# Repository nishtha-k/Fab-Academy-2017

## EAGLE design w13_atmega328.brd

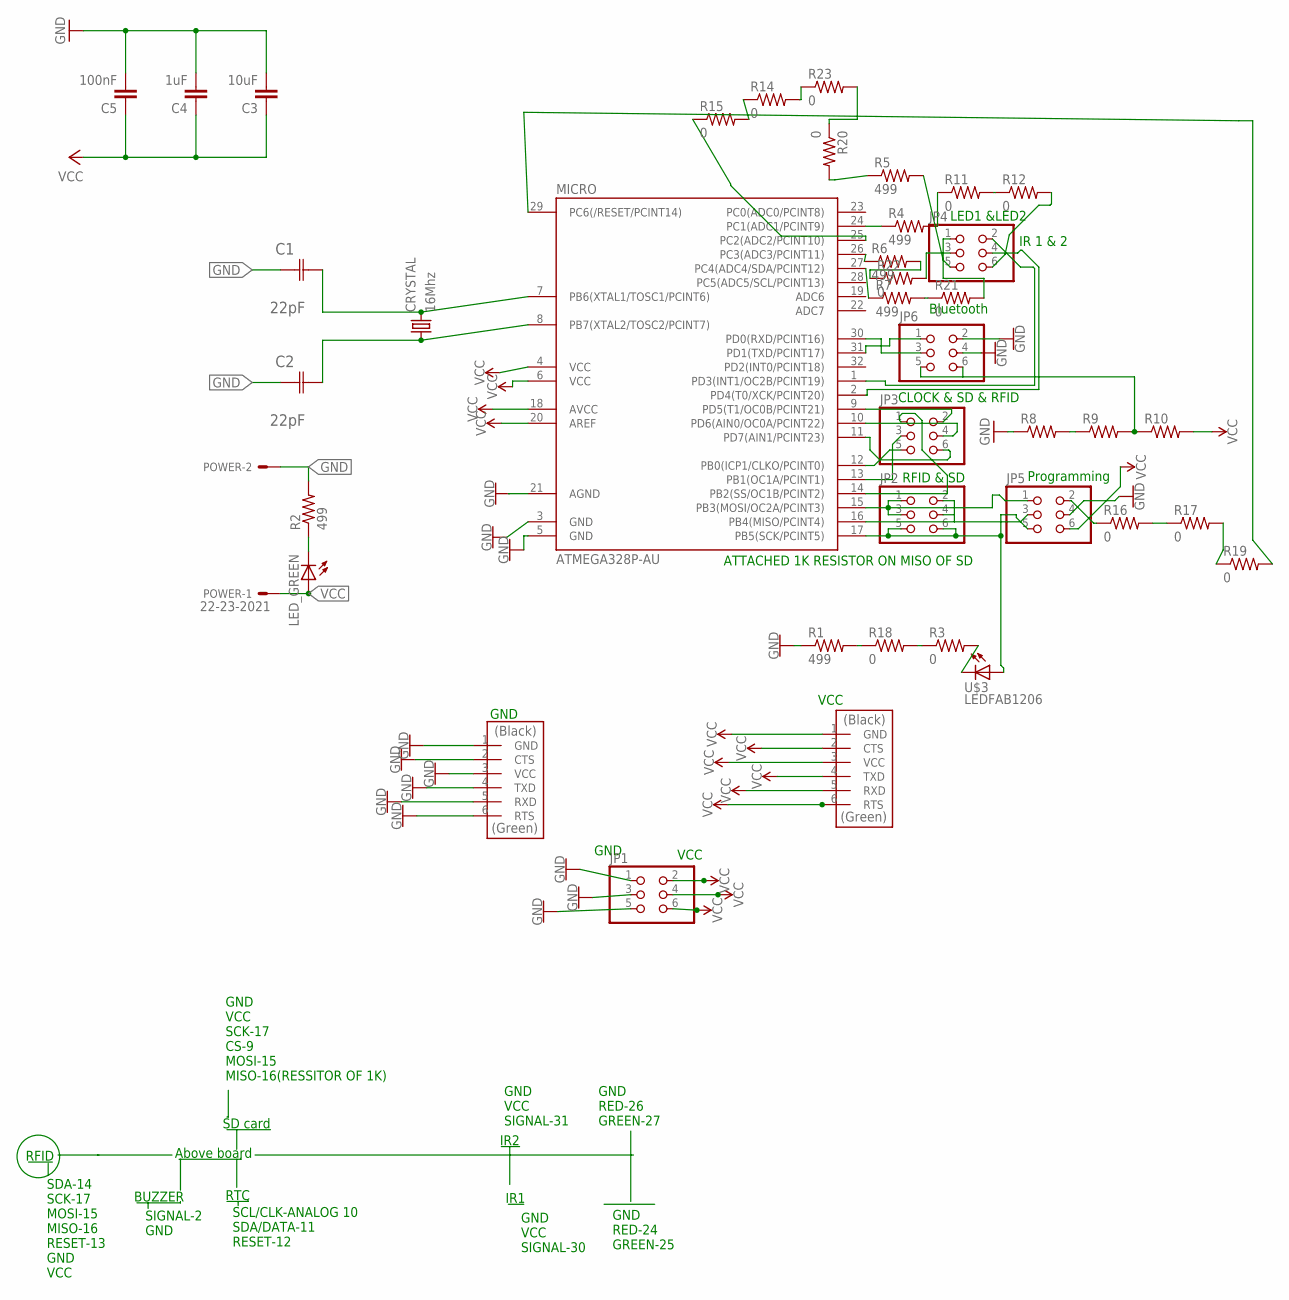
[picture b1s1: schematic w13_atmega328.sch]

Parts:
C1, C2: 22pF; CAPC3216X178N
C3: 10uF; 1206
C4: 1uF; 1206
C5: 100nF; 1206
CRYSTAL: 16Mhz; CSM-7X-DU
JP1, JP2, JP3, JP4, JP5, JP6: PINHD-2X3-SMD; 2X03SMD
LED_GREEN: LED1206; 1206
MICRO: ATMEGA328P-AU; TQFP32-08
POWER: 22-23-2021
R1: 499; R1206
R2: 499; 1206
R3, R11, R12, R14, R15, R16, R17, R18, R19, R20, R21, R22, R23: 0; R1206FAB
R4, R5, R6, R7: 499; R1206FAB
R8, R9, R10: RES-US1206FAB; R1206FAB
U$1, U$2: FTDI-SMD-HEADER; 1X06SMD
U$3: LEDFAB1206; LED1206FAB

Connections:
GND: C1.1 (C1), C2.1 (C1), C3.2, C4.2, C5.2, JP1.1, JP1.3, JP1.5, JP5.4, JP6.2, JP6.4, MICRO.3 (GND), MICRO.5 (GND), POWER.2, R1.1, R2.2, R8.1, U$1.1 (GND), U$1.2 (CTS), U$1.3 (VCC), U$1.4 (TXD), U$1.5 (RXD), U$1.6 (RTS)
unnamed: R4.2, R11.1
unnamed: C1.2 (C2), CRYSTAL.2, MICRO.7 (PB6(XTAL1/TOSC1/PCINT6))
unnamed: JP2.1, JP2.3, JP5.1, MICRO.15 (PB3(MOSI/OC2A/PCINT3))
unnamed: JP3.1, MICRO.14 (PB2(SS/OC1B/PCINT2))
unnamed: JP3.3, MICRO.13 (PB1(OC1A/PCINT1))
unnamed: JP3.5, MICRO.12 (PB0(ICP1/CLKO/PCINT0))
unnamed: JP3.6, MICRO.11 (PD7(AIN1/PCINT23))
unnamed: JP3.2, MICRO.9 (PD5(T1/OC0B/PCINT21))
unnamed: C2.2 (C2), CRYSTAL.1, MICRO.8 (PB7(XTAL2/TOSC2/PCINT7))
unnamed: JP2.5, JP2.6, JP5.5, MICRO.17 (PB5(SCK/PCINT5)), U$3.1 (A)
unnamed: JP3.4, MICRO.10 (PD6(AIN0/OC0A/PCINT22))
unnamed: MICRO.29 (PC6(/RESET/PCINT14)), R19.2
unnamed: R1.2, R18.1
unnamed: MICRO.24 (PC1(ADC1/PCINT9)), R4.1
unnamed: MICRO.25 (PC2(ADC2/PCINT10)), R15.1
unnamed: MICRO.26 (PC3(ADC3/PCINT11)), R6.1
unnamed: JP6.3, MICRO.30 (PD0(RXD/PCINT16))
unnamed: JP6.1, MICRO.31 (PD1(TXD/PCINT17))
unnamed: MICRO.27 (PC4(ADC4/SDA/PCINT12)), R7.1
unnamed: LED_GREEN.2 (C), R2.1
unnamed: JP4.5, R5.2
unnamed: JP4.3, R22.2
unnamed: JP4.6, R12.2
unnamed: JP4.2, MICRO.1 (PD3(INT1/OC2B/PCINT19))
unnamed: R3.2, U$3.2 (C)
unnamed: JP4.1, R21.2
unnamed: R8.2, R9.1
unnamed: JP6.5, JP6.6, R9.2, R10.1
unnamed: JP4.4, MICRO.2 (PD4(T0/XCK/PCINT20))
unnamed: R11.2, R12.1
unnamed: JP2.2, JP2.4, JP5.3, MICRO.16 (PB4(MISO/PCINT4))
unnamed: R14.1, R15.2
unnamed: R14.2, R23.1
unnamed: JP5.2, R16.1
unnamed: R16.2, R17.1
unnamed: R3.1, R18.2
unnamed: R17.2, R19.1
unnamed: R5.1, R20.2
unnamed: R7.2, R21.1
unnamed: R6.2, R22.1
unnamed: R20.1, R23.2
VCC: C3.1, C4.1, C5.1, JP1.2, JP1.4, JP1.6, JP5.6, LED_GREEN.1 (A), MICRO.4 (VCC), MICRO.6 (VCC), MICRO.18 (AVCC), MICRO.20 (AREF), POWER.1, R10.2, U$2.1 (GND), U$2.2 (CTS), U$2.3 (VCC), U$2.4 (TXD), U$2.5 (RXD), U$2.6 (RTS)

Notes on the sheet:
GND
VCC
Programming
RFID & SD
CLOCK & SD & RFID
LED1 &LED2
ATTACHED 1K RESISTOR ON MISO OF SD
RFID
Above board
SD card
RTC
BUZZER
IR1
IR2
SDA-14 SCK-17 MOSI-15 MISO-16 RESET-13 GND VCC
SIGNAL-2 GND
SCL/CLK-ANALOG 10 SDA/DATA-11 RESET-12
GND VCC SIGNAL-30
GND VCC SIGNAL-31
GND VCC SCK-17 CS-9 MOSI-15 MISO-16(RESSITOR OF 1K)
GND RED-26 GREEN-27
GND RED-24 GREEN-25
Bluetooth
IR 1 & 2

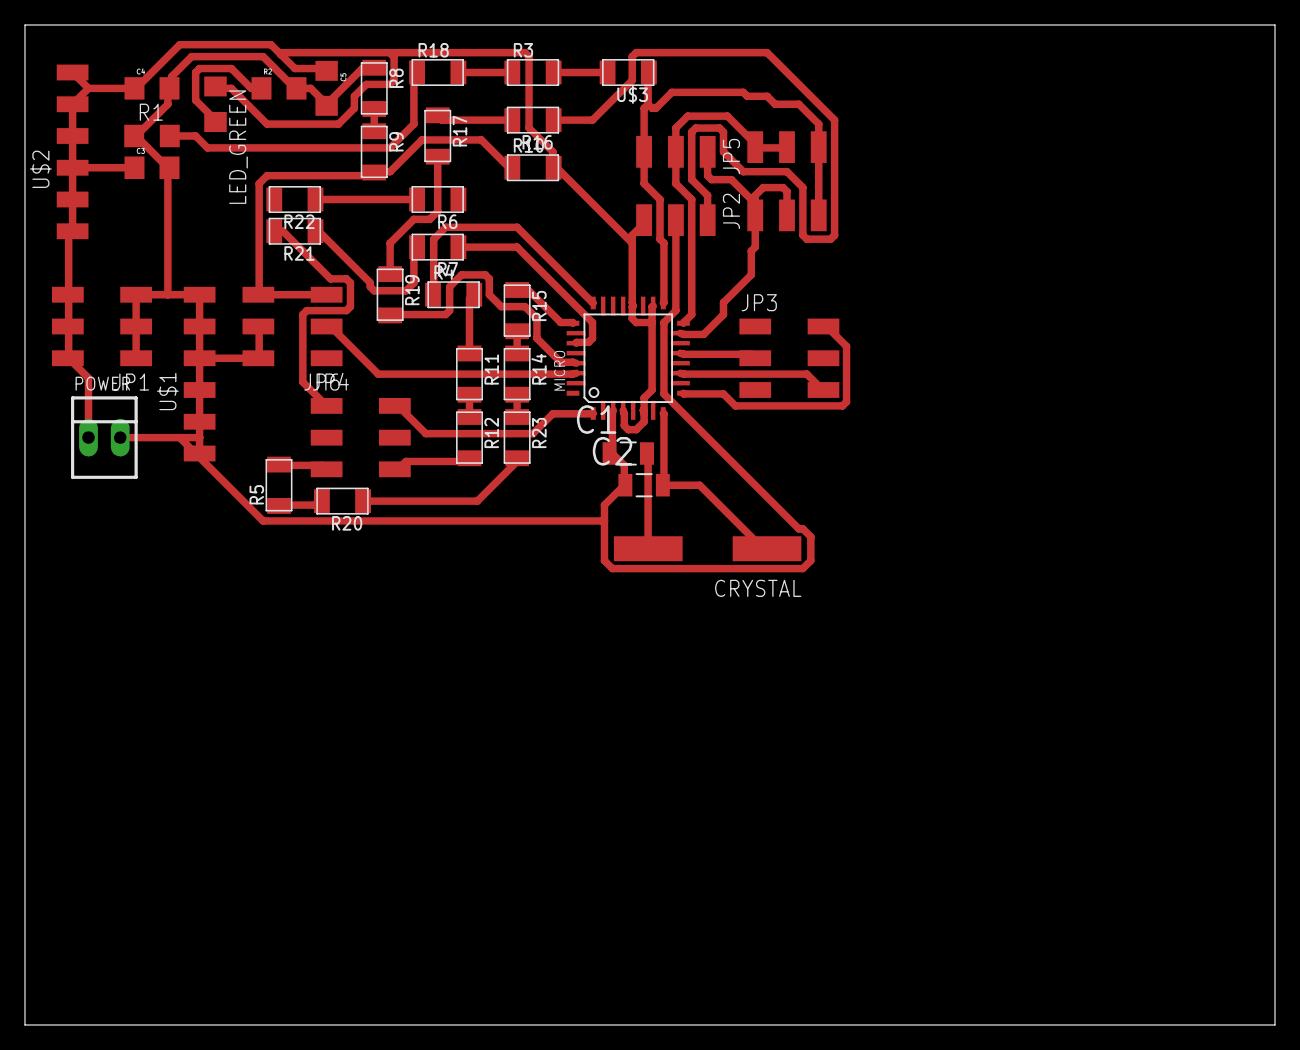
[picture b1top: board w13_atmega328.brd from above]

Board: 2 copper layers, 100.0 x 80.0 mm, 40 parts (0 on the bottom side), 43 nets.

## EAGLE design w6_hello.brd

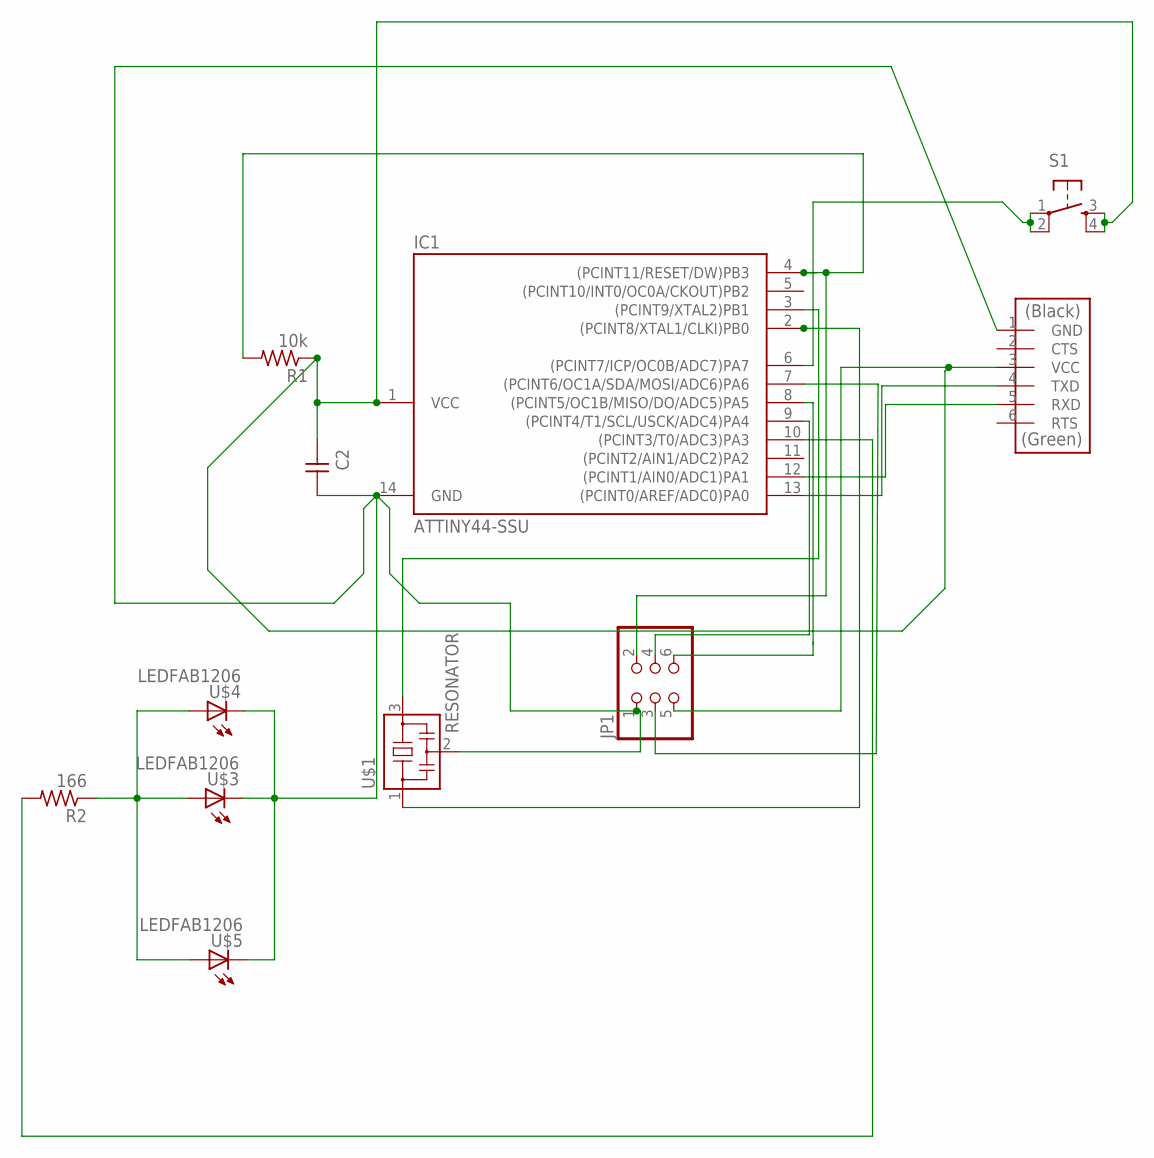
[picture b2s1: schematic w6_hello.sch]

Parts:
C2: CAP-UNPOLARIZEDFAB; C1206FAB
IC1: ATTINY44-SSU; SOIC14
JP1: PINHD-2X3-SMD; 2X03SMD
R1: 10k; R1206
R2: 166; R1206
S1: 6MM_SWITCH6MM_SWITCH; 6MM_SWITCH
U$1: RESONATOR; EFOBM
U$2: FTDI-SMD-HEADER; 1X06SMD
U$3, U$4, U$5: LEDFAB1206; LED1206FAB

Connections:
unnamed: R2.1, U$3.1 (A), U$4.1 (A), U$5.1 (A)
unnamed: IC1.10 ((PCINT3/T0/ADC3)PA3), R2.2
unnamed: C2.1, IC1.1 (VCC), JP1.5, R1.1, S1.3 (S), S1.4 (S1), U$2.3 (VCC)
unnamed: IC1.4 ((PCINT11/RESET/DW)PB3), JP1.2, R1.2
unnamed: IC1.7 ((PCINT6/OC1A/SDA/MOSI/ADC6)PA6), JP1.3
unnamed: IC1.2 ((PCINT8/XTAL1/CLKI)PB0), U$1.1
unnamed: C2.2, IC1.14 (GND), JP1.1, U$1.2, U$2.1 (GND), U$3.2 (C), U$4.2 (C), U$5.2 (C)
unnamed: IC1.3 ((PCINT9/XTAL2)PB1), U$1.3
unnamed: IC1.9 ((PCINT4/T1/SCL/USCK/ADC4)PA4), JP1.4
unnamed: IC1.8 ((PCINT5/OC1B/MISO/DO/ADC5)PA5), JP1.6
unnamed: IC1.13 ((PCINT0/AREF/ADC0)PA0), U$2.4 (TXD)
unnamed: IC1.12 ((PCINT1/AIN0/ADC1)PA1), U$2.5 (RXD)
unnamed: IC1.6 ((PCINT7/ICP/OC0B/ADC7)PA7), S1.1, S1.2 (P1)

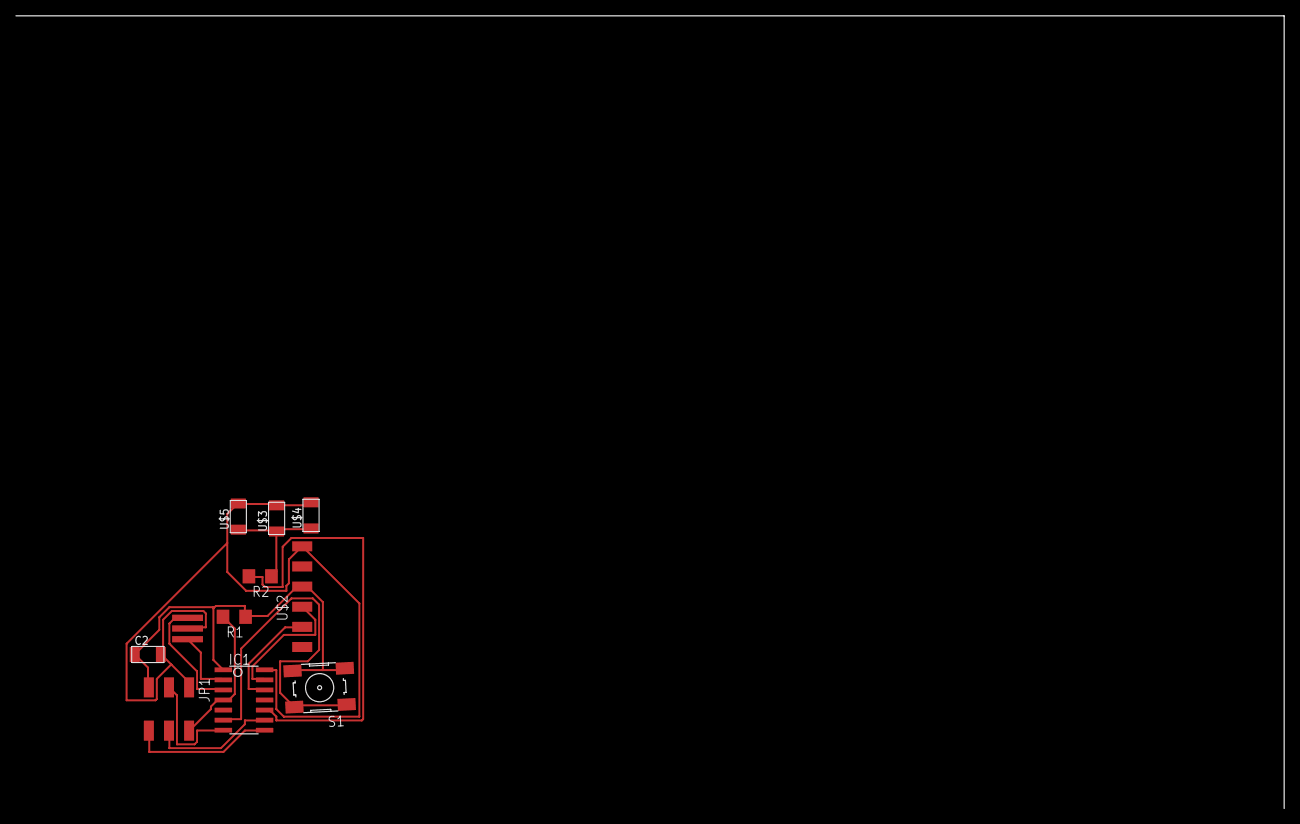
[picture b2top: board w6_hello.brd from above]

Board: 2 copper layers, 160.0 x 100.0 mm, 11 parts (0 on the bottom side), 13 nets.

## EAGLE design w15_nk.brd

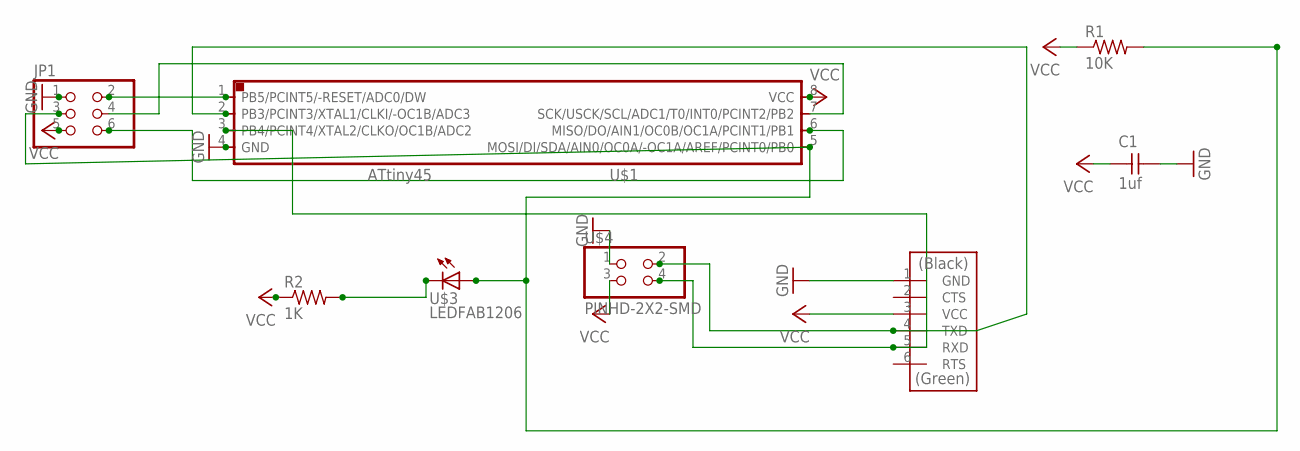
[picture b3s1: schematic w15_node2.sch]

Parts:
C1: 1uf; C1206FAB
JP1: PINHD-2X3-SMD; 2X03SMD
R1: 10K; R1206FAB
R2: 1K; R1206FAB
U$1: ATTINY45SI; SOIC8
U$2: FTDI-SMD-HEADER; 1X06SMD
U$3: LEDFAB1206; LED1206FAB
U$4: PINHD-2X2-SMD; 2X02SMD

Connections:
GND: C1.2, JP1.1, U$1.4 (GND), U$2.1 (GND), U$4.1
unnamed: U$1.2 (PB3/PCINT3/XTAL1/CLKI/-OC1B/ADC3), U$2.4 (TXD), U$4.2
unnamed: U$1.3 (PB4/PCINT4/XTAL2/CLKO/OC1B/ADC2), U$2.5 (RXD), U$4.4
unnamed: JP1.4, U$1.7 (SCK/USCK/SCL/ADC1/T0/INT0/PCINT2/PB2)
unnamed: JP1.3, R1.2, U$1.5 (MOSI/DI/SDA/AIN0/OC0A/-OC1A/AREF/PCINT0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), U$3.1 (A)
unnamed: JP1.2, U$1.1 (PB5/PCINT5/-RESET/ADC0/DW)
unnamed: JP1.6, U$1.6 (MISO/DO/AIN1/OC0B/OC1A/PCINT1/PB1)
unnamed: R2.2, U$3.2 (C)
VCC: C1.1, JP1.5, R1.1, R2.1, U$1.8 (VCC), U$2.3 (VCC), U$4.3

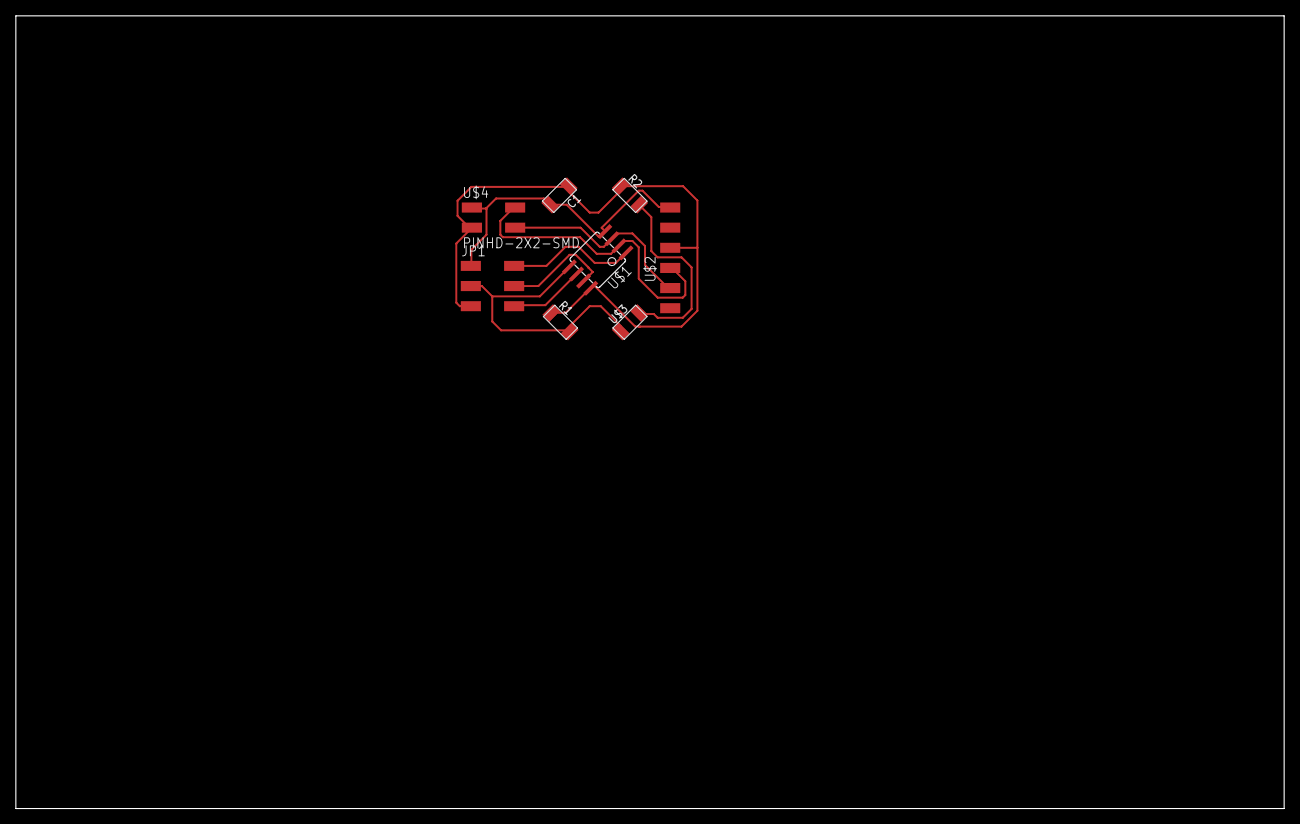
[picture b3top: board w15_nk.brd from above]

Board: 2 copper layers, 160.0 x 100.0 mm, 8 parts (0 on the bottom side), 9 nets.

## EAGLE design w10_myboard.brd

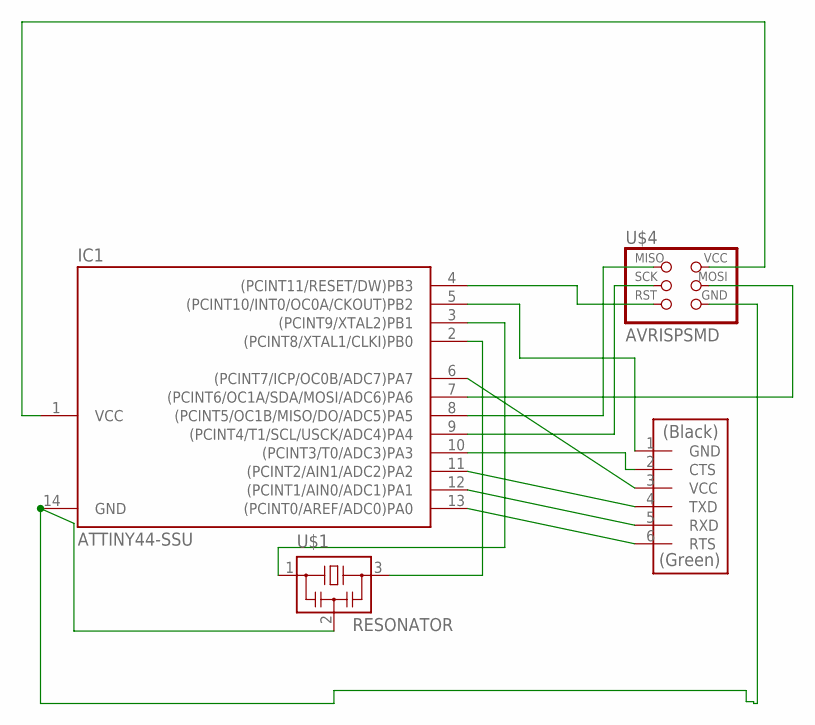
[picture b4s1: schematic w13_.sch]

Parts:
IC1: ATTINY44-SSU; SOIC14
U$1: RESONATOR; EFOBM
U$3: FTDI-SMD-HEADER; 1X06SMD
U$4: AVRISPSMD; 2X03SMD

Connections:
unnamed: IC1.2 ((PCINT8/XTAL1/CLKI)PB0), U$1.3
unnamed: IC1.3 ((PCINT9/XTAL2)PB1), U$1.1
unnamed: IC1.4 ((PCINT11/RESET/DW)PB3), U$4.5 (RST)
unnamed: IC1.7 ((PCINT6/OC1A/SDA/MOSI/ADC6)PA6), U$4.4 (MOSI)
unnamed: IC1.8 ((PCINT5/OC1B/MISO/DO/ADC5)PA5), U$4.1 (MISO)
unnamed: IC1.9 ((PCINT4/T1/SCL/USCK/ADC4)PA4), U$4.3 (SCK)
unnamed: IC1.5 ((PCINT10/INT0/OC0A/CKOUT)PB2), U$3.1 (GND)
unnamed: IC1.1 (VCC), U$4.2 (VCC)
unnamed: IC1.13 ((PCINT0/AREF/ADC0)PA0), U$3.6 (RTS)
unnamed: IC1.12 ((PCINT1/AIN0/ADC1)PA1), U$3.5 (RXD)
unnamed: IC1.11 ((PCINT2/AIN1/ADC2)PA2), U$3.4 (TXD)
unnamed: IC1.10 ((PCINT3/T0/ADC3)PA3), U$3.2 (CTS)
unnamed: IC1.6 ((PCINT7/ICP/OC0B/ADC7)PA7), U$3.3 (VCC)
unnamed: IC1.14 (GND), U$1.2, U$4.6 (GND)

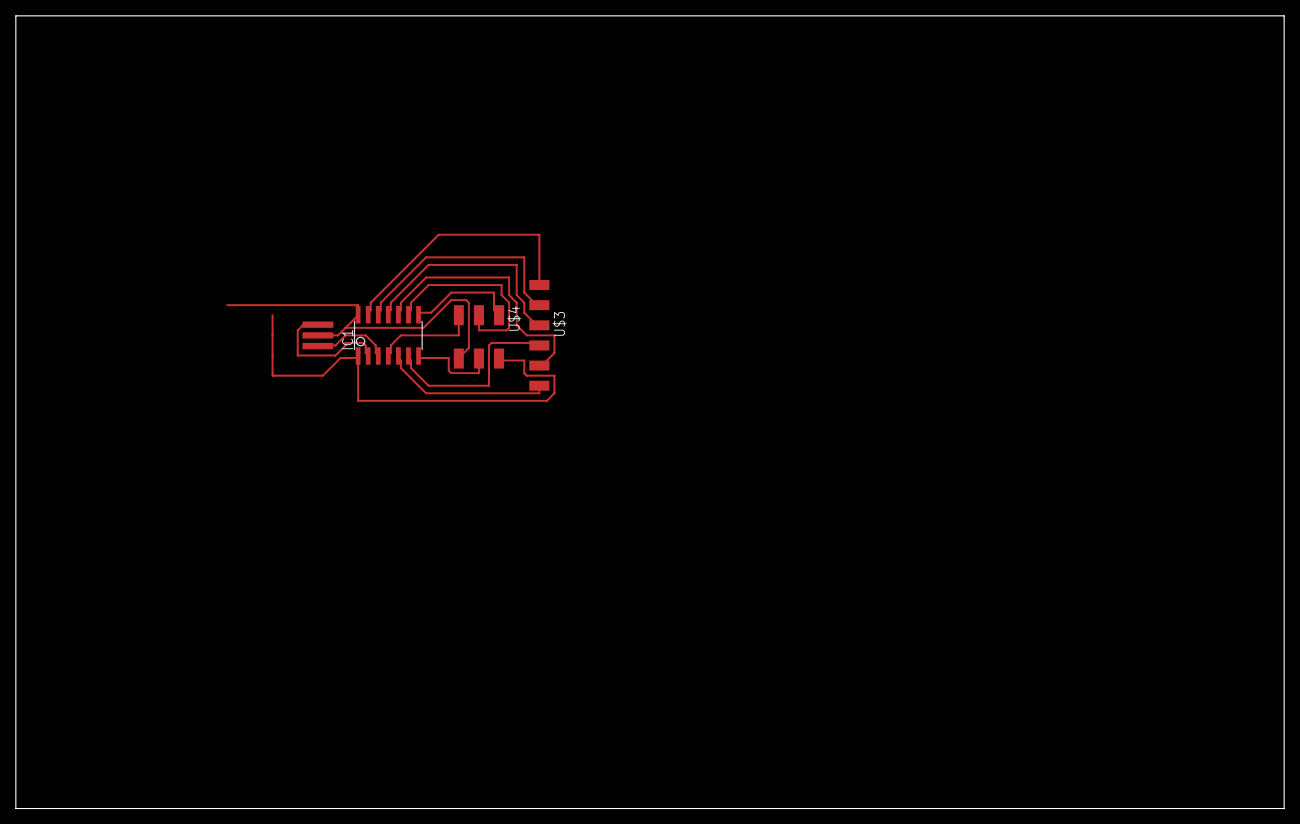
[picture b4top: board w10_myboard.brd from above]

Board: 2 copper layers, 160.0 x 100.0 mm, 4 parts (0 on the bottom side), 14 nets.

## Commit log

2017-05-20 Add files via upload
    week 6 files-Nishtha

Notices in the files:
parts and their libraries:
01_SparkFun: Licensing: CC v3.0 Share-Alike You are welcome to use this library for commercial purposes.
SparkFun-PowerSymbols: Licensing: Creative Commons ShareAlike 4.0 International - https://creativecommons.org/licenses/by-sa/4.0
